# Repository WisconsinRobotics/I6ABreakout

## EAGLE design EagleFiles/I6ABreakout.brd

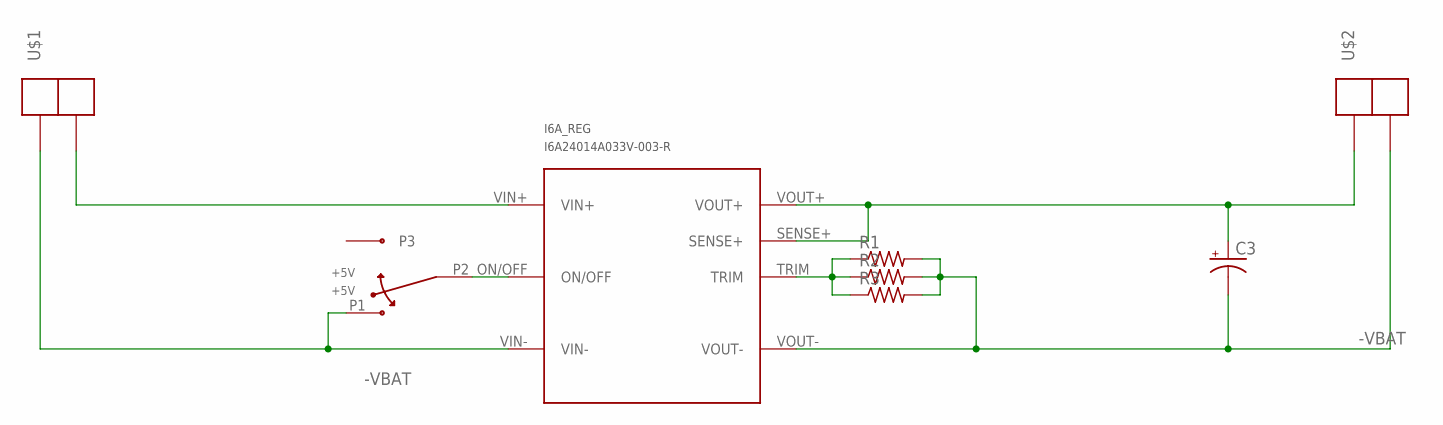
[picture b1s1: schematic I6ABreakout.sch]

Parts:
+5V: +5V; SPDT-TOGGLE
C3: CPOL-USD/7343-31R; D/7343-31R
I6A_REG: I6A24014A033V-003-R; I6A
R1, R2, R3: R-US_M0805; M0805
U$1, U$2: 2PIN-HEADERANDERSON_RIGHTANGLE; ANDERSON_RIGHTANGLE_X2

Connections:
+5V: C3.+, I6A_REG.SENSE+, I6A_REG.VOUT+, U$2.P1
+VBAT: I6A_REG.VIN+, U$1.P2
-VBAT: +5V.P1, C3.-, I6A_REG.VIN-, I6A_REG.VOUT-, R1.2, R2.2, R3.2, U$1.P1, U$2.P2
unnamed: +5V.P2, I6A_REG.ON/OFF
VTRIM1: I6A_REG.TRIM, R1.1, R2.1, R3.1

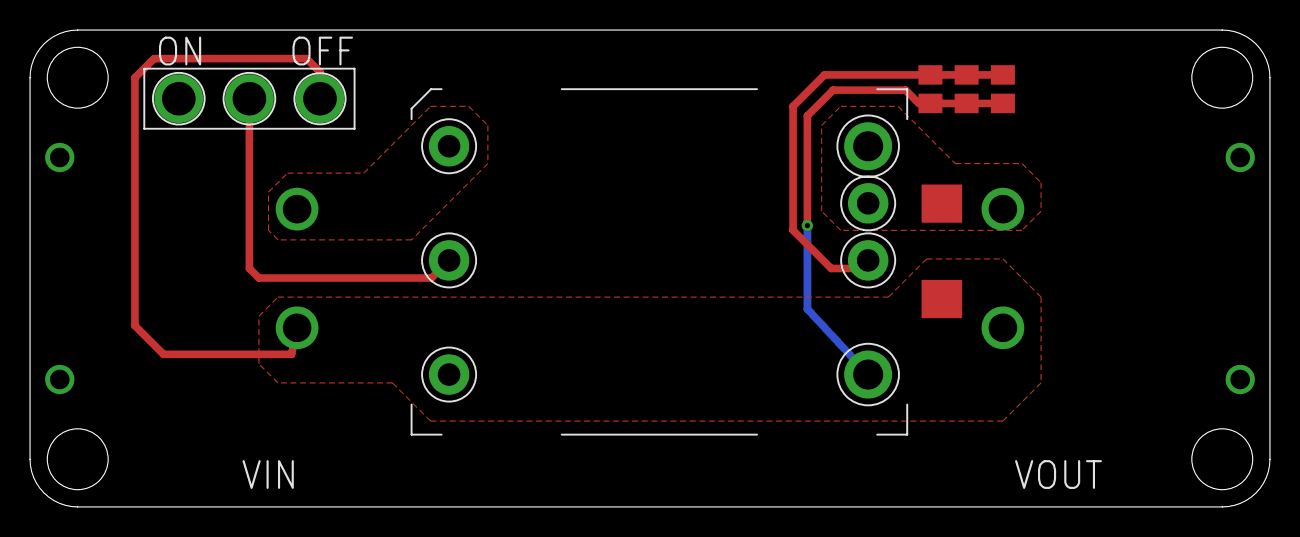
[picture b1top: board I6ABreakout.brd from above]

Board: 2 copper layers, 82.5 x 31.8 mm, 8 parts (0 on the bottom side), 5 nets.

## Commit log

2017-11-10 Initial commit of I6A Breakout eagle files
2017-11-11 Added Inventor files, organized.
